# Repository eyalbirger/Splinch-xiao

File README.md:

# Splinch xiao
this is a 60 keys split ortho col staggered wireless keyboard that uses the 
xiao nrf52840 as its micro controller and zmk as firmwere.

i decided to build this because my current 60% razer gaming keeb, which has really bad software, hurts my wrist, ugly and sounds really annoying.
i got the idea to build this when i saw the ferris sweep on youtube and it looked supppppper cool.

BOM:
| name | quantity | value | lcsc # | price | source | pic |
|:----:|:--------:|:-----:|:------:|:-----:|:------:|:---:|
| choc switches | 62 | - | - | 30$ | https://he.aliexpress.com/item/1005010420712566.html?spm=a2g0o.productlist.main.1.11ab2b90LGevbR&algo_pvid=d8d7e0e8-cffe-4196-91ff-b4abaa745b96&algo_exp_id=d8d7e0e8-cffe-4196-91ff-b4abaa745b96-0&pdp_ext_f=%7B%22order%22%3A%2236%22%2C%22eval%22%3A%221%22%2C%22fromPage%22%3A%22search%22%7D&pdp_npi=6%40dis%21USD%216.36%216.36%21%21%2143.76%2143.76%21%402102f0c917748197491514129eb60f%2112000052353413886%21sea%21IL%217476082455%21X%211%210%21n_tag%3A-29912%3Bd%3A60dc0150%3Bm03_new_user%3A-29895&curPageLogUid=ZHzoQkRR7Oa6&utparam-url=scene%3Asearch%7Cquery_from%3A%7Cx_object_id%3A1005010420712566%7C_p_origin_prod%3A |  |
| choc hot swap socket | 62 | - | - | 20$ | https://he.aliexpress.com/item/33023283633.html?spm=a2g0o.productlist.main.5.625aaiMxaiMxIK&algo_pvid=4ddc268d-7e73-4a14-8662-a3181d01b6c9&algo_exp_id=4ddc268d-7e73-4a14-8662-a3181d01b6c9-4&pdp_ext_f=%7B%22order%22%3A%2240%22%2C%22eval%22%3A%221%22%2C%22fromPage%22%3A%22search%22%7D&pdp_npi=6%40dis%21USD%2113.03%2113.03%21%21%2113.03%2113.03%21%40213ba0c517748199308948942ed8d1%2167259936710%21sea%21IL%217476082455%21X%211%210%21n_tag%3A-29912%3Bd%3A60dc0150%3Bm03_new_user%3A-29895&curPageLogUid=z1nXS3cwvgxl&utparam-url=scene%3Asearch%7Cquery_from%3A%7Cx_object_id%3A33023283633%7C_p_origin_prod%3A |  |
| diodes | 62 | 1N4148W (SOD-123) | C2128 |
| resistor | 2 | 0805, 2M | C106170 | 
| resistor | 2 | 0805, 806k | C63494 |
| keycaps | 62 | - | - | 27$ | https://he.aliexpress.com/item/1005010385514024.html?spm=a2g0o.productlist.main.7.3c216a2cTzDzSy&algo_pvid=79fb82ab-d5dc-4773-af73-70ee35ab3c04&algo_exp_id=79fb82ab-d5dc-4773-af73-70ee35ab3c04-6&pdp_ext_f=%7B%22order%22%3A%2234%22%2C%22eval%22%3A%221%22%2C%22fromPage%22%3A%22search%22%7D&pdp_npi=6%40dis%21USD%213.95%213.41%21%21%213.95%213.41%21%40212a6e2917748200627686778ebed9%2112000052228852476%21sea%21IL%217476082455%21X%211%210%21n_tag%3A-29912%3Bd%3A60dc0150%3Bm03_new_user%3A-29895&curPageLogUid=Ni8of9UZsCqr&utparam-url=scene%3Asearch%7Cquery_from%3A%7Cx_object_id%3A1005010385514024%7C_p_origin_prod%3A |  |
| nrf52 xiao | 2 | - | - | 40$ | https://he.aliexpress.com/item/1005006988954136.html?spm=a2g0o.productlist.main.1.57ce40b4QXnPng&algo_pvid=f9b91e77-0c87-4e99-935a-fb38f1f5f0a7&algo_exp_id=f9b91e77-0c87-4e99-935a-fb38f1f5f0a7-0&pdp_ext_f=%7B%22order%22%3A%222000%22%2C%22spu_best_type%22%3A%22price%22%2C%22eval%22%3A%221%22%2C%22fromPage%22%3A%22search%22%7D&pdp_npi=6%40dis%21USD%2118.24%2110.58%21%21%21125.54%2172.81%21%402140e67317748203008007890e5056%2112000042942288177%21sea%21IL%217476082455%21X%211%210%21n_tag%3A-29912%3Bd%3A60dc0150%3Bm03_new_user%3A-29895&curPageLogUid=wBoNLOG3rDIr&utparam-url=scene%3Asearch%7Cquery_from%3A%7Cx_object_id%3A1005006988954136%7C_p_origin_prod%3A |  |
| switch | 2 | MSK12C02 | - |
| screws | 8 | m2 | - |
| silicone feet | some | - | - | 7$ | https://he.aliexpress.com/item/1005010241201821.html?spm=a2g0o.productlist.main.27.163736427Ym5ki&algo_pvid=df98ee35-a38e-4c63-a4ad-8a2221e94798&algo_exp_id=df98ee35-a38e-4c63-a4ad-8a2221e94798-26&pdp_ext_f=%7B%22order%22%3A%22149%22%2C%22eval%22%3A%221%22%2C%22fromPage%22%3A%22search%22%7D&pdp_npi=6%40dis%21USD%217.39%213.55%21%21%2150.88%2124.42%21%40210141f717748203947087454e4ff5%2112000051650167405%21sea%21IL%217476082455%21X%211%210%21n_tag%3A-29912%3Bd%3A60dc0150%3Bm03_new_user%3A-29895&curPageLogUid=sZyKOcIq8vIl&utparam-url=scene%3Asearch%7Cquery_from%3A%7Cx_object_id%3A1005010241201821%7C_p_origin_prod%3A |  |
| nice nano | 1 | - | - | - | - | - |
| TOTAL | - | - | - | 124$ | - | - |

in order to complete that you also need the pcb. you can choose to use the pcba or assamble it yourself. i reccomend to use the pcba with the ressistors and the doides, and hand soldering the others.
this is the pcb:

this is the case:
you need **8 m2 standoffs**, you can glue them with superglue into the standoff holes.
you also need **8 m2 screws** to screw the pcb to the case.
you can put a **6mm (max) thick battery**.
you need to mirror the case for the left part.

firmware: https://github.com/eyalbirger/zmk-config-splinch.git
i still need to complete and test the firmware (i have like one build error), but it will probably be completed in a few days (i have a war to deal with, so you know...).

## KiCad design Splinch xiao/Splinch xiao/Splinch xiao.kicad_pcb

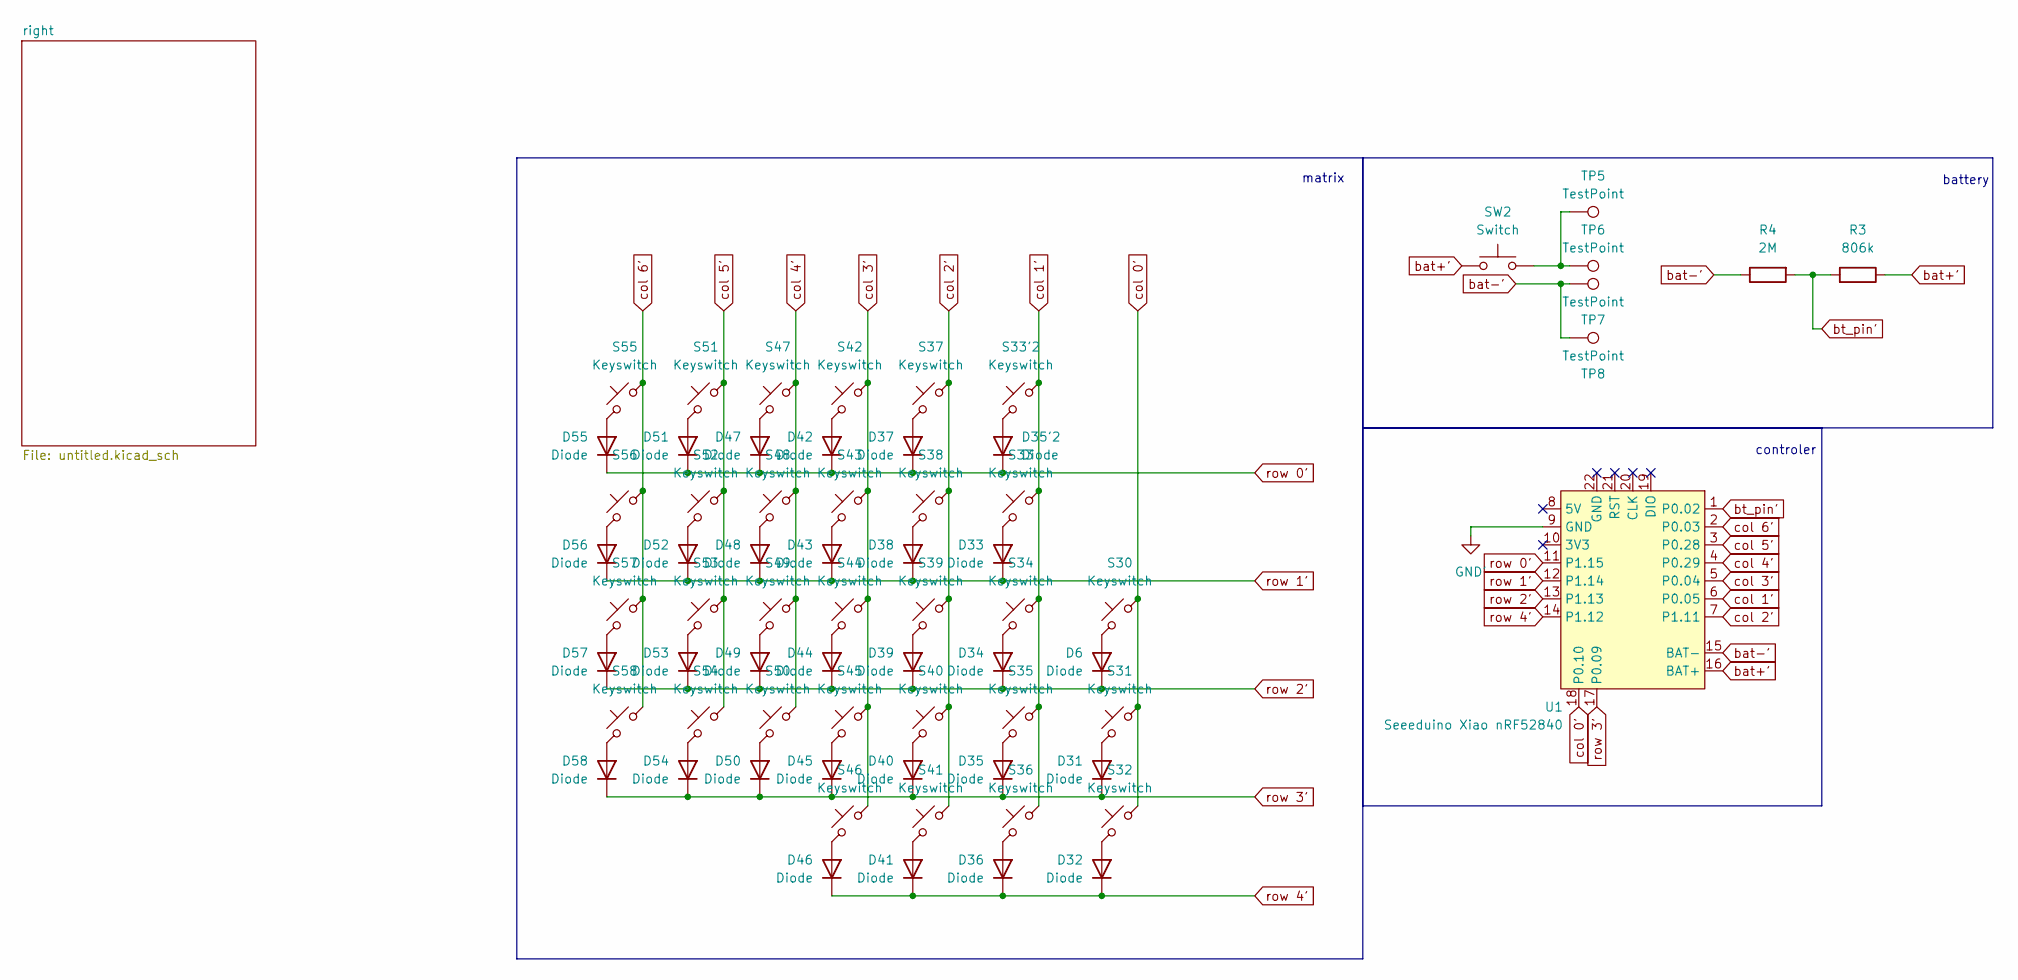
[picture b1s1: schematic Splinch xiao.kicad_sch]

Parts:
D6, D31, D32, D33, D34, D35, D35'2, D36, D37, D38, D39, D40, D41, D42, D43, D44, D45, D46, D47, D48, D49, D50, D51, D52, D53, D54, D55, D56, D57, D58: Diode; Diode_SOD-123; LCSC C2128
R3: 806k; R_0805_2012Metric_Pad1.20x1.40mm_HandSolder; LCSC C121025
R4: 2M; R_0805_2012Metric_Pad1.20x1.40mm_HandSolder; LCSC C106170
S30, S31, S32, S33, S33'2, S34, S35, S36, S37, S38, S39, S40, S41, S42, S43, S44, S45, S46, S47, S48, S49, S50, S51, S52, S53, S54, S55, S56, S57, S58: Keyswitch; Kailh_socket_PG1350
SW2: Switch; Switch_MSK12C02
TP5, TP6, TP7, TP8: TestPoint; TestPoint_Pad_D3.0mm
U1: Seeeduino Xiao nRF52840; Xiao_nRF52840_ACH

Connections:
GND': U1.9 (GND)
unnamed: D6.2 (A), S30.2
unnamed: D31.2 (A), S31.2
unnamed: D32.2 (A), S32.2
unnamed: D33.2 (A), S33.2
unnamed: D34.2 (A), S34.2
unnamed: D35'2.2 (A), S33'2.2
unnamed: D35.2 (A), S35.2
unnamed: D36.2 (A), S36.2
unnamed: D37.2 (A), S37.2
unnamed: D38.2 (A), S38.2
unnamed: D39.2 (A), S39.2
unnamed: D40.2 (A), S40.2
unnamed: D41.2 (A), S41.2
unnamed: D42.2 (A), S42.2
unnamed: D43.2 (A), S43.2
unnamed: D44.2 (A), S44.2
unnamed: D45.2 (A), S45.2
unnamed: D46.2 (A), S46.2
unnamed: D47.2 (A), S47.2
unnamed: D48.2 (A), S48.2
unnamed: D49.2 (A), S49.2
unnamed: D50.2 (A), S50.2
unnamed: D51.2 (A), S51.2
unnamed: D52.2 (A), S52.2
unnamed: D53.2 (A), S53.2
unnamed: D54.2 (A), S54.2
unnamed: D55.2 (A), S55.2
unnamed: D56.2 (A), S56.2
unnamed: D57.2 (A), S57.2
unnamed: D58.2 (A), S58.2
unnamed: SW2.2, TP5.1, TP6.1
bat+': R3.1, SW2.1, U1.16 (BAT+)
bat-': R4.1, TP7.1, TP8.1, U1.15 (BAT-)
bt_pin': R3.2, R4.2, U1.1 (P0.02)
col 0': S30.1, S31.1, S32.1, U1.18 (P0.10)
col 1': S33.1, S33'2.1, S34.1, S35.1, S36.1, U1.6 (P0.05)
col 2': S37.1, S38.1, S39.1, S40.1, S41.1, U1.7 (P1.11)
col 3': S42.1, S43.1, S44.1, S45.1, S46.1, U1.5 (P0.04)
col 4': S47.1, S48.1, S49.1, S50.1, U1.4 (P0.29)
col 5': S51.1, S52.1, S53.1, S54.1, U1.3 (P0.28)
col 6': S55.1, S56.1, S57.1, S58.1, U1.2 (P0.03)
row 0': D35'2.1 (K), D37.1 (K), D42.1 (K), D47.1 (K), D51.1 (K), D55.1 (K), U1.11 (P1.15)
row 1': D33.1 (K), D38.1 (K), D43.1 (K), D48.1 (K), D52.1 (K), D56.1 (K), U1.12 (P1.14)
row 2': D6.1 (K), D34.1 (K), D39.1 (K), D44.1 (K), D49.1 (K), D53.1 (K), D57.1 (K), U1.13 (P1.13)
row 3': D31.1 (K), D35.1 (K), D40.1 (K), D45.1 (K), D50.1 (K), D54.1 (K), D58.1 (K), U1.17 (P0.09)
row 4': D32.1 (K), D36.1 (K), D41.1 (K), D46.1 (K), U1.14 (P1.12)

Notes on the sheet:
controler
battery
matrix

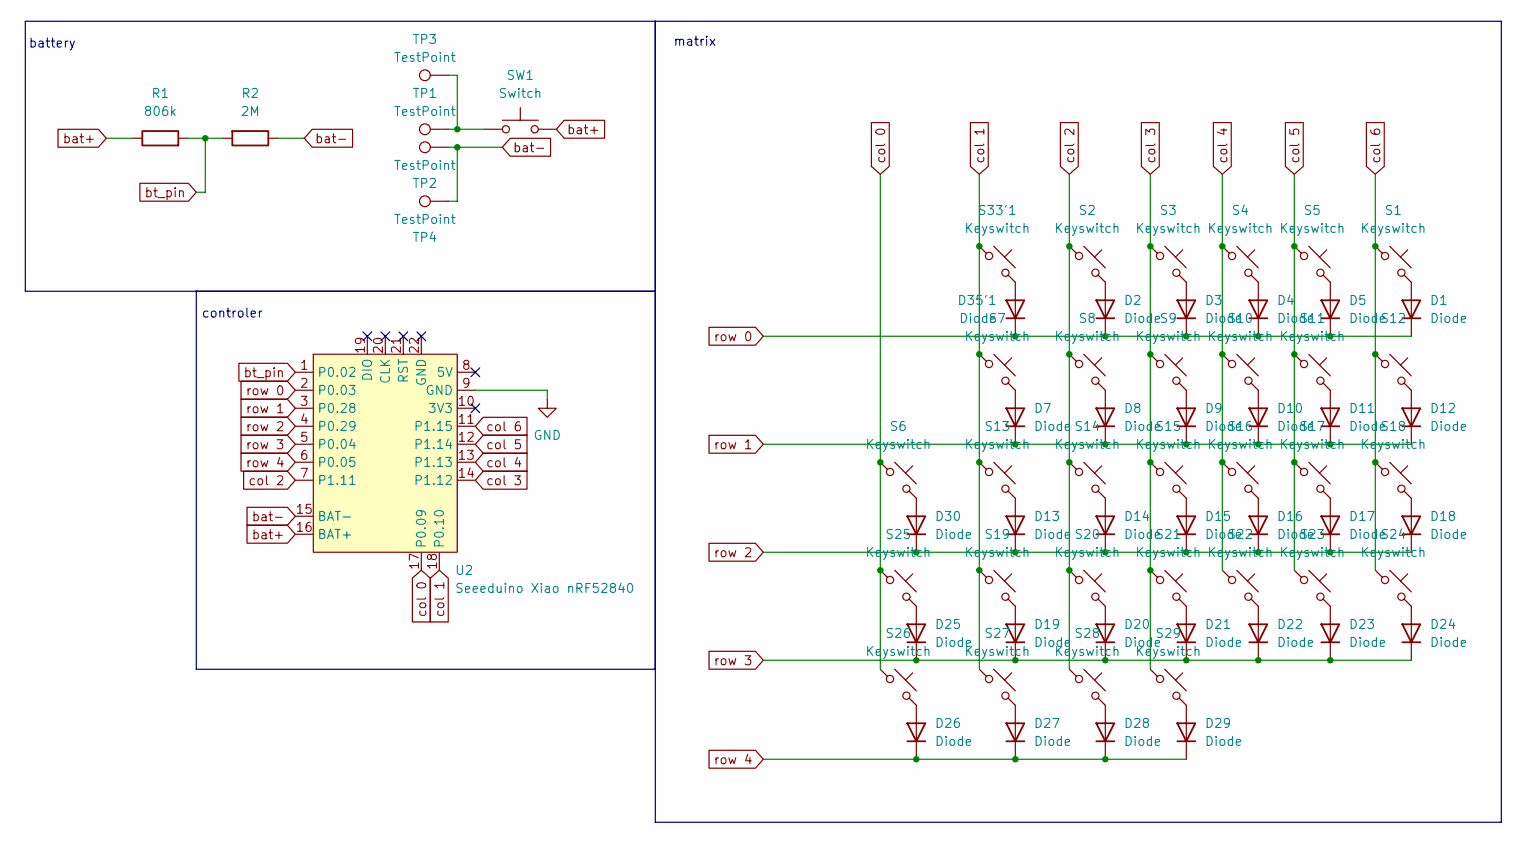
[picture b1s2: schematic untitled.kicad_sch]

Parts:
D1, D2, D3, D4, D5, D7, D8, D9, D10, D11, D12, D13, D14, D15, D16, D17, D18, D19, D20, D21, D22, D23, D24, D25, D26, D27, D28, D29, D30, D35'1: Diode; Diode_SOD-123; LCSC C2128
R1: 806k; R_0805_2012Metric_Pad1.20x1.40mm_HandSolder; LCSC C121025
R2: 2M; R_0805_2012Metric_Pad1.20x1.40mm_HandSolder; LCSC C106170
S1, S2, S3, S4, S5, S6, S7, S8, S9, S10, S11, S12, S13, S14, S15, S16, S17, S18, S19, S20, S21, S22, S23, S24, S25, S26, S27, S28, S29, S33'1: Keyswitch; Kailh_socket_PG1350
SW1: Switch; Switch_MSK12C02
TP1, TP2, TP3, TP4: TestPoint; TestPoint_Pad_D3.0mm
U2: Seeeduino Xiao nRF52840; Xiao_nRF52840_ACH

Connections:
GND: U2.9 (GND)
unnamed: D1.2 (A), S1.2
unnamed: D2.2 (A), S2.2
unnamed: D3.2 (A), S3.2
unnamed: D4.2 (A), S4.2
unnamed: D5.2 (A), S5.2
unnamed: D7.2 (A), S7.2
unnamed: D8.2 (A), S8.2
unnamed: D9.2 (A), S9.2
unnamed: D10.2 (A), S10.2
unnamed: D11.2 (A), S11.2
unnamed: D12.2 (A), S12.2
unnamed: D13.2 (A), S13.2
unnamed: D14.2 (A), S14.2
unnamed: D15.2 (A), S15.2
unnamed: D16.2 (A), S16.2
unnamed: D17.2 (A), S17.2
unnamed: D18.2 (A), S18.2
unnamed: D19.2 (A), S19.2
unnamed: D20.2 (A), S20.2
unnamed: D21.2 (A), S21.2
unnamed: D22.2 (A), S22.2
unnamed: D23.2 (A), S23.2
unnamed: D24.2 (A), S24.2
unnamed: D25.2 (A), S25.2
unnamed: D26.2 (A), S26.2
unnamed: D27.2 (A), S27.2
unnamed: D28.2 (A), S28.2
unnamed: D29.2 (A), S29.2
unnamed: D30.2 (A), S6.2
unnamed: D35'1.2 (A), S33'1.2
unnamed: SW1.2, TP1.1, TP3.1
bat+: R1.1, SW1.1, U2.16 (BAT+)
bat-: R2.1, TP2.1, TP4.1, U2.15 (BAT-)
bt_pin: R1.2, R2.2, U2.1 (P0.02)
col 0: S6.1, S25.1, S26.1, U2.17 (P0.09)
col 1: S7.1, S13.1, S19.1, S27.1, S33'1.1, U2.18 (P0.10)
col 2: S2.1, S8.1, S14.1, S20.1, S28.1, U2.7 (P1.11)
col 3: S3.1, S9.1, S15.1, S21.1, S29.1, U2.14 (P1.12)
col 4: S4.1, S10.1, S16.1, S22.1, U2.13 (P1.13)
col 5: S5.1, S11.1, S17.1, S23.1, U2.12 (P1.14)
col 6: S1.1, S12.1, S18.1, S24.1, U2.11 (P1.15)
row 0: D1.1 (K), D2.1 (K), D3.1 (K), D4.1 (K), D5.1 (K), D35'1.1 (K), U2.2 (P0.03)
row 1: D7.1 (K), D8.1 (K), D9.1 (K), D10.1 (K), D11.1 (K), D12.1 (K), U2.3 (P0.28)
row 2: D13.1 (K), D14.1 (K), D15.1 (K), D16.1 (K), D17.1 (K), D18.1 (K), D30.1 (K), U2.4 (P0.29)
row 3: D19.1 (K), D20.1 (K), D21.1 (K), D22.1 (K), D23.1 (K), D24.1 (K), D25.1 (K), U2.5 (P0.04)
row 4: D26.1 (K), D27.1 (K), D28.1 (K), D29.1 (K), U2.6 (P0.05)

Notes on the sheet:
matrix
controler
battery

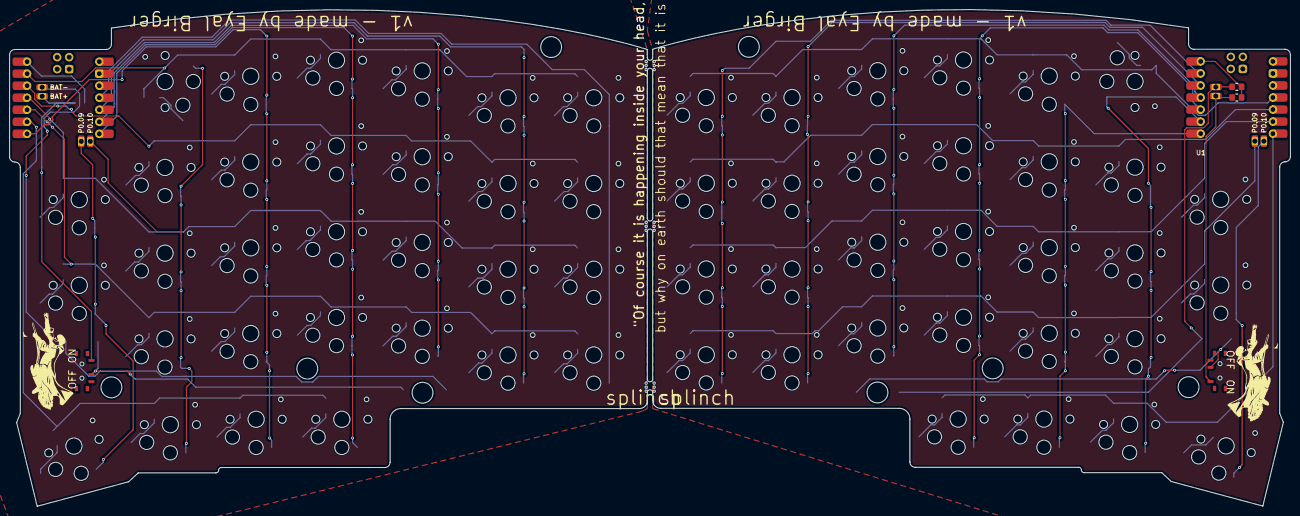
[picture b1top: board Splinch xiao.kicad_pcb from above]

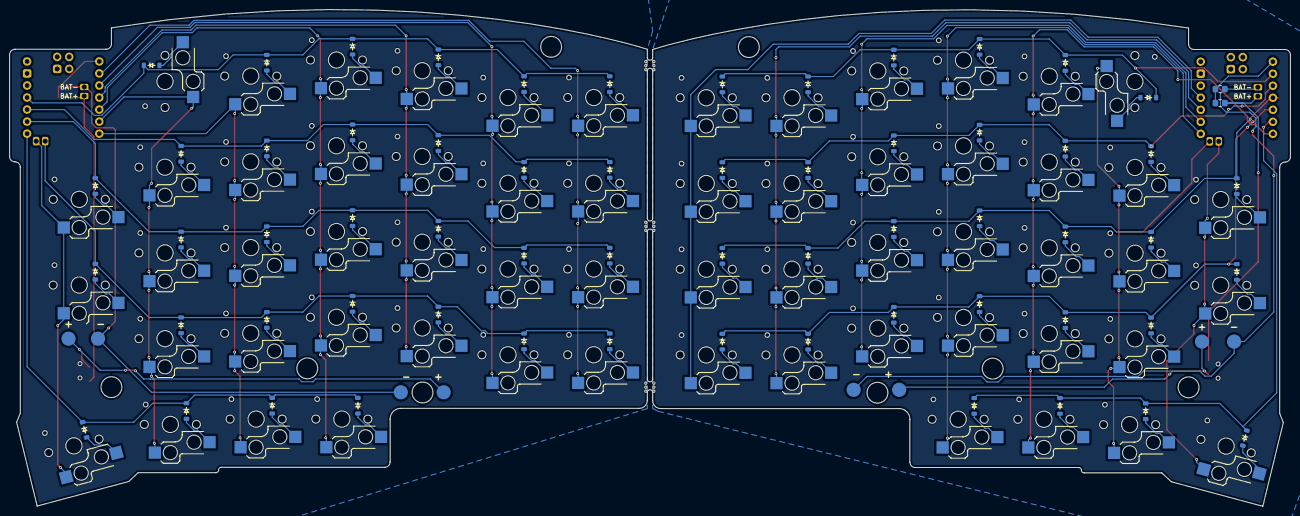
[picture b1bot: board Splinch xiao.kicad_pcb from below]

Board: 2 copper layers, 270.4 x 104.8 mm, 136 parts (70 on the bottom side), 92 nets.

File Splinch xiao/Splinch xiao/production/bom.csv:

Designator,Footprint,Quantity,Value,LCSC Part #
"D1, D10, D11, D12, D13, D14, D15, D16, D17, D18, D19, D2, D20, D21, D22, D23, D24, D25, D26, D27, D28, D29, D3, D30, D31, D32, D33, D34, D35, D35'1, D35'2, D36, D37, D38, D39, D4, D40, D41, D42, D43, D44, D45, D46, D47, D48, D49, D5, D50, D51, D52, D53, D54, D55, D56, D57, D58, D6, D7, D8, D9",Diode_SOD-123,60,Diode,
"R1, R3",0805,2,806k,
"R2, R4",0805,2,2M,
"S1, S10, S11, S12, S13, S14, S15, S16, S17, S18, S19, S2, S20, S21, S22, S23, S24, S25, S26, S27, S28, S29, S3, S30, S31, S32, S33, S33'1, S33'2, S34, S35, S36, S37, S38, S39, S4, S40, S41, S42, S43, S44, S45, S46, S47, S48, S49, S5, S50, S51, S52, S53, S54, S55, S56, S57, S58, S6, S7, S8, S9",Kailh_socket_PG1350,60,Keyswitch,
"SW1, SW2",Switch_MSK12C02,2,Switch,
"TP1, TP2, TP3, TP4, TP5, TP6, TP7, TP8",TestPoint_Pad_D3.0mm,8,TestPoint,

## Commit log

2026-01-18 schem + pcb
2026-01-26 outline and left schem
2026-01-26 did some of the other galf
2026-03-29 case' wiring and more
2026-03-29 added silk screen and reade me
2026-03-29 garber for the new pcb
2026-03-29 updated readne
2026-03-29 readme
2026-03-31 broski
2026-04-01 readme, cad
2026-05-02 case left and readme
